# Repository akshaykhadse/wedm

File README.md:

# Power Supply Design for Wire EDM Cutting of Silicon

Part of project titled *Modelling and Control of Wire Electro Discharge Machining Processes for Cutting of Silicon Wafers*.

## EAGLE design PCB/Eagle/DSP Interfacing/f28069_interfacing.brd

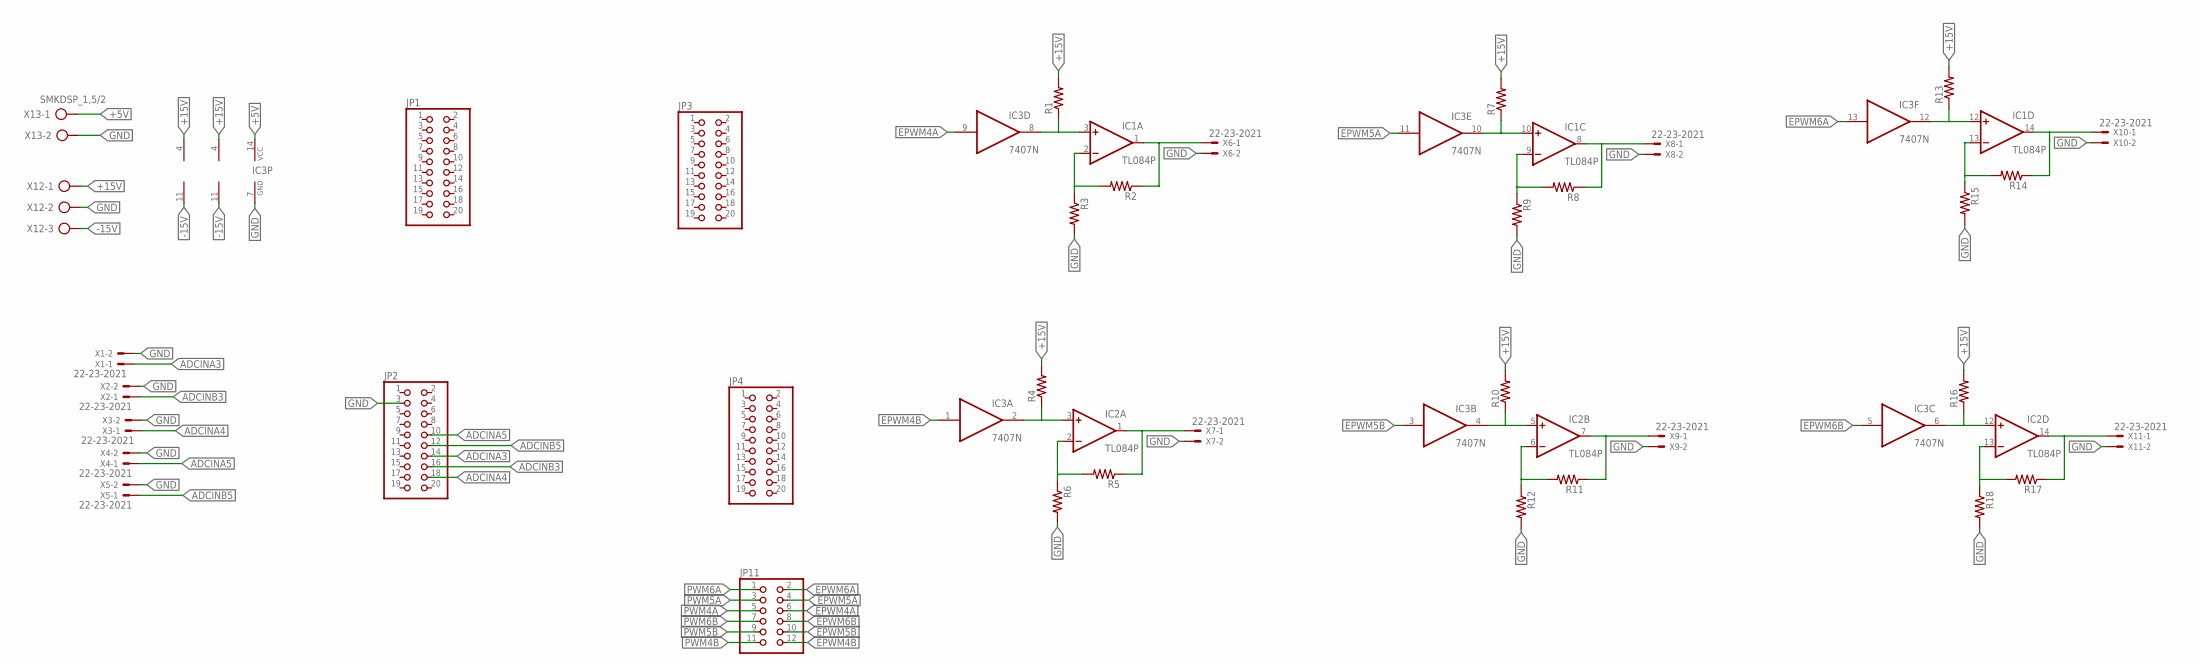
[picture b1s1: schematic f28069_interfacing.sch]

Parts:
IC1, IC2: TL084P; DIL14
IC3: 7407N; DIL14
JP1, JP2, JP3, JP4: PINHD-2X10; 2X10
JP11: PINHD-2X6; 2X06
R1, R2, R3, R4, R5, R6, R7, R8, R9, R10, R11, R12, R13, R14, R15, R16, R17, R18: R-US_0207/10; 0207/10
X1, X2, X3, X4, X5, X6, X7, X8, X9, X10, X11: 22-23-2021
X12: AK300/3
X13: SMKDSP_1,5/2

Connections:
+5V: IC3.14 (VCC), X13.1
+15V: IC1.4 (V+), IC2.4 (V+), R1.2, R4.2, R7.2, R10.2, R13.2, R16.2, X12.1
-15V: IC1.11 (V-), IC2.11 (V-), X12.3
ADCINA3: JP2.14, X1.1
ADCINA4: JP2.18, X3.1
ADCINA5: JP2.10, X4.1
ADCINB3: JP2.16, X2.1
ADCINB5: JP2.12, X5.1
EPWM4A: IC3.9 (I), JP11.6
EPWM4B: IC3.1 (I), JP11.12
EPWM5A: IC3.11 (I), JP11.4
EPWM5B: IC3.3 (I), JP11.10
EPWM6A: IC3.13 (I), JP11.2
EPWM6B: IC3.5 (I), JP11.8
GND: IC3.7 (GND), JP2.3, R3.2, R6.2, R9.2, R12.2, R15.2, R18.2, X1.2, X2.2, X3.2, X4.2, X5.2, X6.2, X7.2, X8.2, X9.2, X10.2, X11.2, X12.2, X13.2
unnamed: IC1.2 (-IN), R2.2, R3.1
unnamed: IC1.1 (OUT), R2.1, X6.1
unnamed: IC1.3 (+IN), IC3.8 (O), R1.1
unnamed: IC2.1 (OUT), R5.1, X7.1
unnamed: IC2.3 (+IN), IC3.2 (O), R4.1
unnamed: IC2.2 (-IN), R5.2, R6.1
unnamed: IC1.8 (OUT), R8.1, X8.1
unnamed: IC1.10 (+IN), IC3.10 (O), R7.1
unnamed: IC1.9 (-IN), R8.2, R9.1
unnamed: IC2.7 (OUT), R11.1, X9.1
unnamed: IC2.5 (+IN), IC3.4 (O), R10.1
unnamed: IC2.6 (-IN), R11.2, R12.1
unnamed: IC1.14 (OUT), R14.1, X10.1
unnamed: IC1.12 (+IN), IC3.12 (O), R13.1
unnamed: IC1.13 (-IN), R14.2, R15.1
unnamed: IC2.14 (OUT), R17.1, X11.1
unnamed: IC2.12 (+IN), IC3.6 (O), R16.1
unnamed: IC2.13 (-IN), R17.2, R18.1
PWM4A: JP11.5
PWM4B: JP11.11
PWM5A: JP11.3
PWM5B: JP11.9
PWM6A: JP11.1
PWM6B: JP11.7

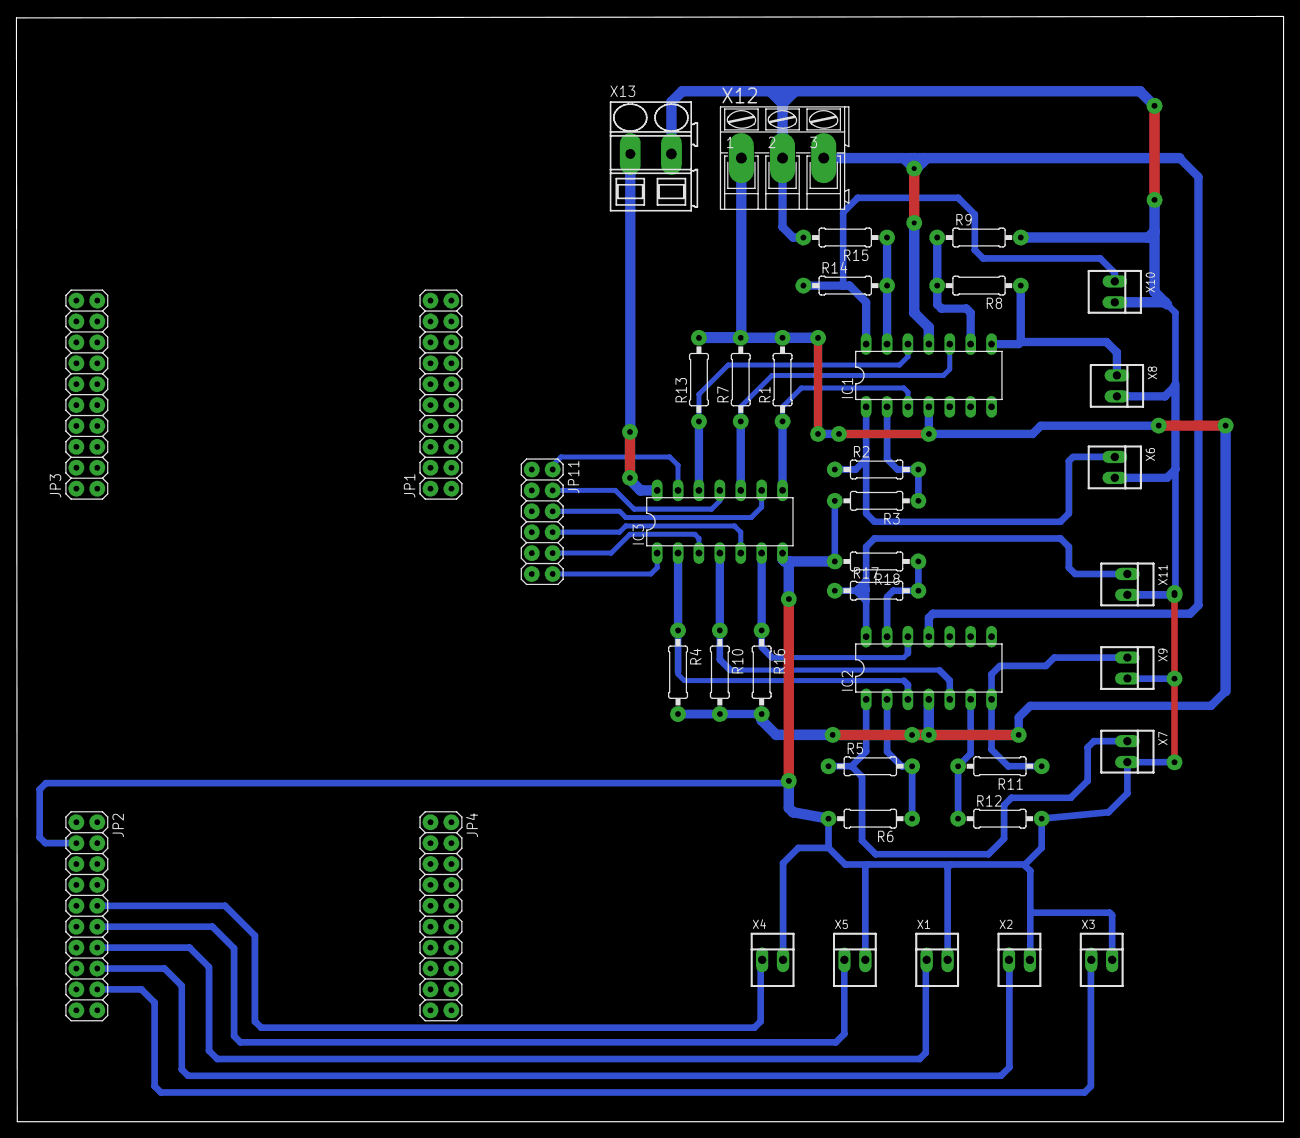
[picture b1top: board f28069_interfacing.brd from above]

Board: 2 copper layers, 154.0 x 134.3 mm, 39 parts (0 on the bottom side), 33 nets.

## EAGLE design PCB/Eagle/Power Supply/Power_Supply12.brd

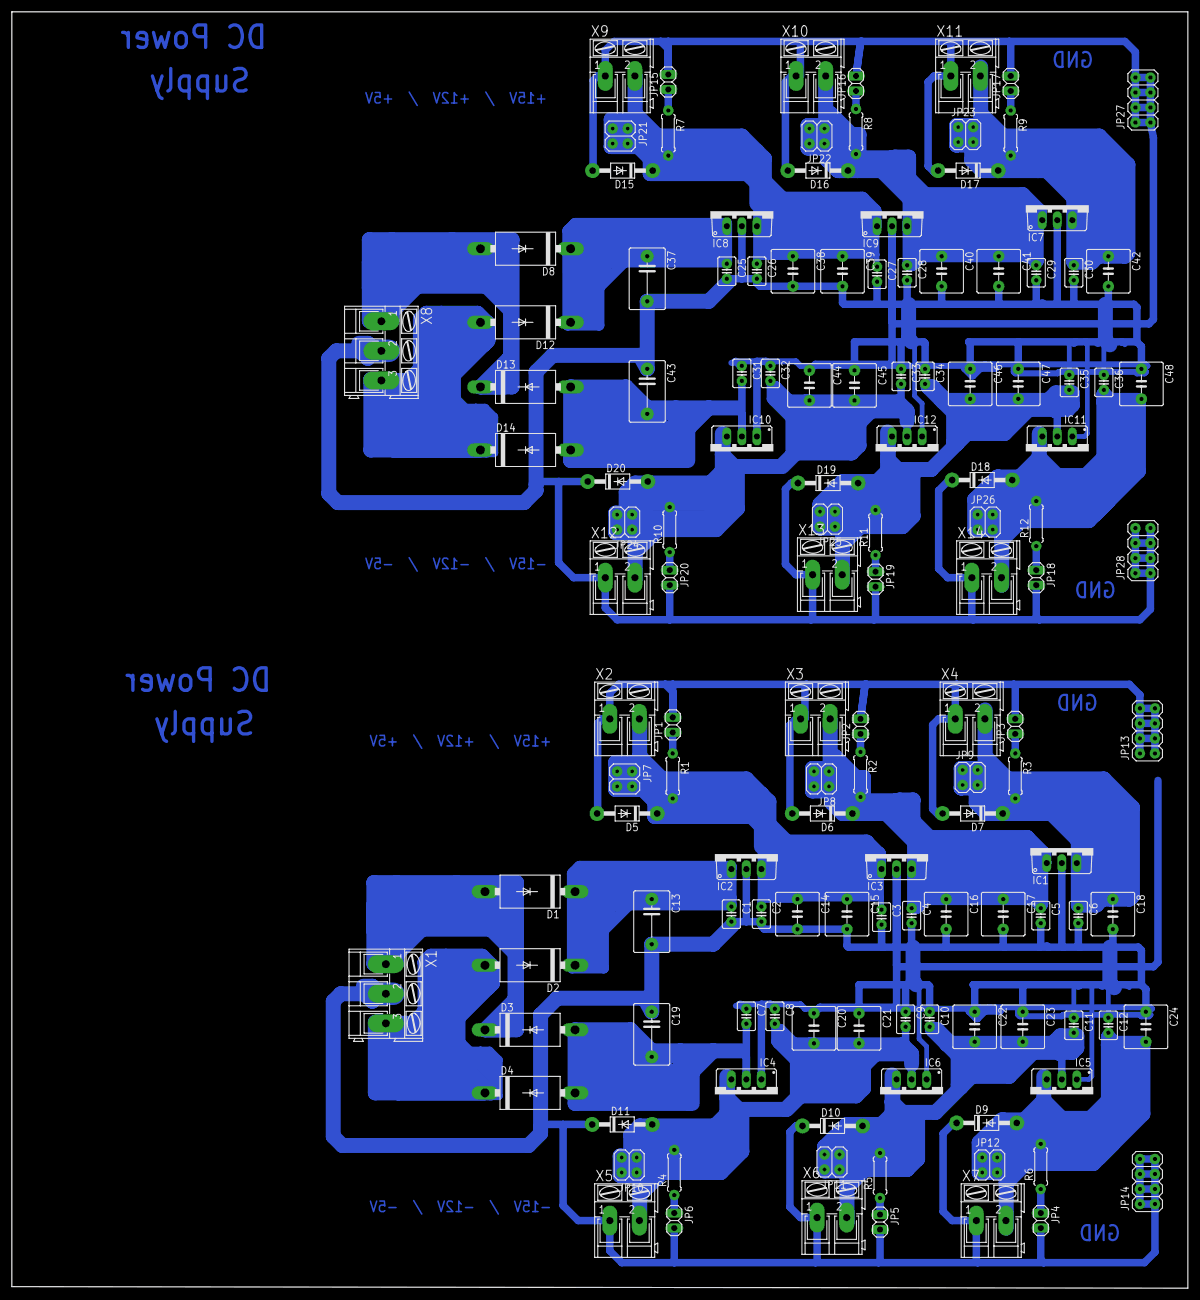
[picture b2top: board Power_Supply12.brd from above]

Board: 2 copper layers, 198.9 x 215.8 mm, 134 parts (0 on the bottom side), 34 nets.

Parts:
C1, C2, C3, C4, C5, C6, C7, C8, C9, C10, C11, C12, C25, C26, C27, C28, C29, C30, C31, C32, C33, C34, C35, C36: C025-030X050
C13, C19, C37, C43: C075-063X106
C14, C15, C16, C17, C18, C20, C21, C22, C23, C24, C38, C39, C40, C41, C42, C44, C45, C46, C47, C48: C050-075X075
D1, D2, D3, D4, D8, D12, D13, D14: 1N5400; DO201-15
D5, D6, D7, D9, D10, D11, D15, D16, D17, D18, D19, D20: 1N4004; DO41-10
IC1, IC7: 7805TV; TO220V
IC2, IC8: 7815TV; TO220V
IC3, IC9: 7812TV; TO220V
IC4, IC5, IC6, IC10, IC11, IC12: 79XXS
JP1, JP2, JP3, JP4, JP5, JP6, JP15, JP16, JP17, JP18, JP19, JP20: 1X02
JP7, JP8, JP9, JP10, JP11, JP12, JP21, JP22, JP23, JP24, JP25, JP26: 2X02
JP13, JP14, JP27, JP28: 2X04
R1, R2, R3, R4, R5, R6, R7, R8, R9, R10, R11, R12: 0207/7
X1, X8: AK300/3
X2, X3, X4, X5, X6, X7, X9, X10, X11, X12, X13, X14: AK300/2

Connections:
unnamed: C1.1, C13.1, D1.C, D2.C, IC2.1
unnamed: JP20.1, R10.1
unnamed: C2.1, C3.1, C14.1, C15.1, D5.C, IC2.3, IC3.1, JP7.1, JP7.2, JP7.3, JP7.4, R1.2, X2.2
unnamed: JP19.1, R11.1
unnamed: JP18.1, R12.1
unnamed: D2.A, D4.C, X1.3
unnamed: C1.2, C2.2, C3.2, C4.2, C5.2, C6.2, C7.1, C8.1, C9.1, C10.1, C11.1, C12.1, C13.2, C14.2, C15.2, C16.2, C17.2, C18.2, C19.1, C20.1, C21.1, C22.1, C23.1, C24.1, D5.A, D6.A, D7.A, D9.C, D10.C, D11.C, IC1.2, IC2.2, IC3.2, IC4.GND, IC5.GND, IC6.GND, JP1.2, JP2.2, JP3.2, JP4.2, JP5.2, JP6.2, JP13.1, JP13.2, JP13.3, JP13.4, JP13.5, JP13.6, JP13.7, JP13.8, JP14.1, JP14.2, JP14.3, JP14.4, JP14.5, JP14.6, JP14.7, JP14.8, X1.2, X2.1, X3.1, X4.1, X5.1, X6.1, X7.1
unnamed: C4.1, C5.1, C16.1, C17.1, D6.C, IC1.1, IC3.3, JP8.1, JP8.2, JP8.3, JP8.4, R2.2, X3.2
unnamed: JP17.1, R9.1
unnamed: C6.1, C18.1, D7.C, IC1.3, JP9.1, JP9.2, JP9.3, JP9.4, R3.2, X4.2
unnamed: JP6.1, R4.1
unnamed: JP16.1, R8.1
unnamed: JP5.1, R5.1
unnamed: JP4.1, R6.1
unnamed: JP15.1, R7.1
unnamed: JP3.1, R3.1
unnamed: D8.A, D13.C, X8.1
unnamed: JP2.1, R2.1
unnamed: JP1.1, R1.1
unnamed: D1.A, D3.C, X1.1
unnamed: C8.2, C9.2, C20.2, C21.2, D11.A, IC4.OUT, IC6.IN, JP10.1, JP10.2, JP10.3, JP10.4, R4.2, X5.2
unnamed: C10.2, C11.2, C22.2, C23.2, D10.A, IC5.IN, IC6.OUT, JP11.1, JP11.2, JP11.3, JP11.4, R5.2, X6.2
unnamed: C7.2, C19.2, D3.A, D4.A, IC4.IN
unnamed: C31.2, C43.2, D13.A, D14.A, IC10.IN
unnamed: C12.2, C24.2, D9.A, IC5.OUT, JP12.1, JP12.2, JP12.3, JP12.4, R6.2, X7.2
unnamed: C25.1, C37.1, D8.C, D12.C, IC8.1
unnamed: C26.1, C27.1, C38.1, C39.1, D15.C, IC8.3, IC9.1, JP21.1, JP21.2, JP21.3, JP21.4, R7.2, X9.2
unnamed: C28.1, C29.1, C40.1, C41.1, D16.C, IC7.1, IC9.3, JP22.1, JP22.2, JP22.3, JP22.4, R8.2, X10.2
unnamed: C30.1, C42.1, D17.C, IC7.3, JP23.1, JP23.2, JP23.3, JP23.4, R9.2, X11.2
unnamed: C32.2, C33.2, C44.2, C45.2, D20.A, IC10.OUT, IC12.IN, JP24.1, JP24.2, JP24.3, JP24.4, R10.2, X12.2
unnamed: C34.2, C35.2, C46.2, C47.2, D19.A, IC11.IN, IC12.OUT, JP25.1, JP25.2, JP25.3, JP25.4, R11.2, X13.2
unnamed: C36.2, C48.2, D18.A, IC11.OUT, JP26.1, JP26.2, JP26.3, JP26.4, R12.2, X14.2
unnamed: D12.A, D14.C, X8.3
unnamed: C25.2, C26.2, C27.2, C28.2, C29.2, C30.2, C31.1, C32.1, C33.1, C34.1, C35.1, C36.1, C37.2, C38.2, C39.2, C40.2, C41.2, C42.2, C43.1, C44.1, C45.1, C46.1, C47.1, C48.1, D15.A, D16.A, D17.A, D18.C, D19.C, D20.C, IC7.2, IC8.2, IC9.2, IC10.GND, IC11.GND, IC12.GND, JP15.2, JP16.2, JP17.2, JP18.2, JP19.2, JP20.2, JP27.1, JP27.2, JP27.3, JP27.4, JP27.5, JP27.6, JP27.7, JP27.8, JP28.1, JP28.2, JP28.3, JP28.4, JP28.5, JP28.6, JP28.7, JP28.8, X8.2, X9.1, X10.1, X11.1, X12.1, X13.1, X14.1

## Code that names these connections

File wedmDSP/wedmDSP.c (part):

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//! - log      => Logged Values
//
//! Pin Connections:
//! - ADCINA4 => Pin69
//! - ADCINB3 => Pin68
//! - ADCINA3 => Pin67
//! - ADCINB5 => Pin66
//! - ADCINA5 => Pin65
//!
//! - EPWM4A  => Pin80
//! - EPWM4B  => Pin79
//! - EPWM5A  => Pin78
//! - EPWM5B  => Pin77
//! - EPWM6A  => Pin76
//! - EPWM6B  => Pin75
//!
//! - GPIO22 => Pin8
//!
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#define EPWM4_CLKDIV 0 //EPWM4 CLKDIV

#define EPWM5_PER 4560     // EPWM5 Period
#define EPWM5A_DUTY 0.2    // EPWM5A Duty
#define EPWM5B_DUTY 0   // EPWM5B Duty
#define EPWM5_HSPCLKDIV 0 //EPWM5 HSPCLKDIV
#define EPWM5_CLKDIV 0 //EPWM5 CLKDIV

#define EPWM6_PER 9500     // EPWM6 Period
#define EPWM6A_DUTY 0.5    // EPWM6A Duty
#define EPWM6B_DUTY 0   // EPWM6B Duty
#define EPWM6_HSPCLKDIV 3 //EPWM6 HSPCLKDIV
#define EPWM6_CLKDIV 4 //EPWM6 CLKDIV

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    AdcRegs.ADCCTL2.bit.CLKDIV4EN   = 0;

    // Channel select for SOCs
    AdcRegs.ADCSOC0CTL.bit.CHSEL    = 5;    // set SOC0 channel select to ADCINA5
    AdcRegs.ADCSOC1CTL.bit.CHSEL    = 13;   // set SOC1 channel select to ADCINB5
    AdcRegs.ADCSOC2CTL.bit.CHSEL    = 3;    // set SOC2 channel select to ADCINA3
    AdcRegs.ADCSOC3CTL.bit.CHSEL    = 11;   // set SOC3 channel select to ADCINB3
    AdcRegs.ADCSOC4CTL.bit.CHSEL    = 4;    // set SOC4 channel select to ADCINA4

    // Set SOC0 start trigger on CPU TIMER 0 Interrupt
    // due to round-robin SOC0 converts in order SOC0, SOC1, ..., SOC4
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
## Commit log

2017-09-13 Stylised PID Model
2017-09-13 Added Snubber Calculations
    - Added Snubber Calculations for Qd in mast_conv.m in PID
    - Updated Model accordingly
    `
2017-09-13 Created Folder for Dependencies
    - Created seperate folder for dependencies like syms2tf
    - Updated 04 PID/mast_conv.m accordingly
    ** Common files would reside in this directory from now on
2017-09-14 Updated for 50 KHz
    - Updated PID model for 50 KHz
    - Added README.md
2017-09-14 Changed Machining Time to 200us
    - Changed Machining time to 200us
    - Added conversion to discrete time TF
2017-09-14 Tuned PID Controllers
    - Tuned PID Controllers
    - Added delay between Current and Voltage source operation
    - Modified README.md
2017-09-14 Added documentation
2017-09-14 Set theme jekyll-theme-cayman
2017-09-14 Added Download Links
2017-09-14 Moving docs to gh-pages branch
2017-09-16 Simulated Tastekin Paper
    - Simulated Tastekin paper in `05 Tastekin` folder
    - Updated component list
2017-09-18 RC Snubber
    - Renamed PID simulation file
    - Reset Qd Simulink Block parameters to all default values
    - Implemented RC Snubber (Diode is commented)
    - Recorded waveforms and circuit
    - Corrected the names of switches in load
2017-09-18 Implemented RCD Snubber
    - Uncommented diode
    - Recorded waveforms
2017-09-18 Finalised RC Snubber
2017-09-18 Changed Measurement Blocks' Names
2017-09-18 Fixed D1 Scope
2017-09-18 Updated PID
    - Split master_cov.m
    - Added Compensator blocks
    - Compensator blocks ane not yet tuned
2017-09-21 Updated Component Sheet
    - Changed BOM1.xlsx
    - Added Datat generation code
2017-09-26 Working 2
    - Deduced logic for l and c values
2017-09-27 Current Mode Control
    - Using PID
    - 100 time original L1 value
2017-09-29 Working 2
    - Fixed logic for device selection
    - Tuned Controllers
    - Fixed PWM Issue
2017-10-05 Corrected Comments
2017-10-12 Changed folder structure and cleanup
    - Removed incorrect files
    - Moved everythinh to root
    - Spreadsheet for component values now moved to google drive
2017-10-12 Renamed Files
2017-10-12 Consolidated everything
2017-12-11 Before Stage 2
2018-01-04 Updated Structure
2018-02-11 Add PCB design files and slide programs
    - PCB design files in root/PCB
    - Slide programs in root/Slide Programs
2018-02-11 Changes as of 25th Jan, 2018
    - Add floating scopes and scope viewers
    - Split master_conv2 script
    - Add power calculations
2018-02-12 Add comparison of current source with normal buck converter
2018-02-14 Fixed SVG files not showing
    - Removed *.svg from .gitignore
2018-02-15 Add comparison with normal files and CAD model
    - Add files for comparison of voltage and current source with normal
    buck converter. Run 'master1.m' to use
    - Add SolidWorks model
2018-02-15 Fix voltage source bug
    - Fixed the issue of compensator on modified voltage source causing
    instability
2018-02-15 Add plots for SRG Talk
    - Add bode and pz plots for SRG talk to 'Documentation/srg_plots'
2018-02-26 Prepare for SRG talk
    - Imporve graphs
    - Display poles
    - Improve comparison between normal and modified buck converter topologies
2018-03-01 Add Discrete Controller
    - Add discre current and voltage source controller using discrete tf
    block
2018-03-03 Fix Discrete Controllers
    - Make VS controller usinf z^-1 blocks
    - Add ZOH Block
    - Change Simulation type to continous from powergui
    - Previous error was due to sampling period of 0.01*1/f_sw in powergui block
2018-03-27 Add PCB files from Proteus
    - Cleaned up DipTrace PCB files
    - Added Proteus PCB files
2018-04-06 Change figures for PDES paper
    - Reduce size of buck converter comparison figures
    - Corrected Qd in conv-top-master
2018-04-06 Add pole locus plot script and debug end to end run
    - Add script 'pole_locus.m' to plot variation of poles of both the sources with change in values of L and C
    - Naming conventions improved in 'compensator_design.m' and 'modelling.m' to avoid replacing transfer fuctions.
    - Naming conventions improved in 'normal_buck_comparison_cs.m' and 'normal_buck_comparison_cs.m' to avoid replacing of compensator numerators and denominators, and original transfer functions
    - Hard coded 'c2_val' from 'master_conv2.m' at the end of 'normal_buck_comparison_cs.m'
2018-04-07 Match upto Makarand's paper changes - 1
    - Add dicscrete compenstor for current source using basic blocks
    - Add pulsed reference in PID for current source and corresponding vlaue
    changes
    - Sanitize 'mast_conv2.m'. Move clearing part to 'master1.m'
    - Stylize all the scopes and zooms (not completed)
2018-04-07 Match upto Makarand's paper changes - 1
    - Fixed controller scopes issue
2018-04-07 Add code to generate figures
    - Add code to generate required figures for PDES Paper in 'master1.m'
2018-04-07 Add more PDES paper figures script
    - Backup and restore logic for temperorily changed variables refined
    - Seperate script for PDES figures generation.
    - Added variation of poles with passive component values
2018-04-07 Removed obsolete files
2018-04-10 Improvements to paper figures
    - rl1 and rl2 increased
    - Optimised 'ploes_locus.m' and 'pdes_figures.m'
    - PDES figures exported to PDF
    - Naming improved in 'normal_buck_comparison_*s.m' files
2018-04-11 Add equations to PDES figures
    - Add equations ot comparison figures
    - Add 'convert_pdf.bat' to convert svg to pdfs
2018-04-12 Add compenstor bode plots in pdes formatting
    - Added code in 'pdes_figures.m' to format compensator performance bode
    plots
    - Fixed pdf cropping in matlab generated figures
2018-04-12 Minor naming improvements
2018-04-14 Update diagrams, Change rl1 value
    - Updated 2quad and buck svg files with i0hat or v0hat/dhat
    - rl1 value changed to 100uH (Courtesy Mak) and updated all pdes
    diagrams
    - Added plot for current source inductor power
    - Changed reference selection in 'powersupply.slx' to variable based
    switch
2018-04-30 Add DSP code
    - Add DSP CCS project in 'wedmDSP' directory
    - Paste 'wedmDSP' directory in 'C:\ti\c2000\C2000Ware_1_00_04_00\device_support\f2806x\examples\c28'
2018-05-02 Add ADC code to wedmDSP
2018-05-02 Add ePWM code to wedmDSP
2018-05-11 Working DSP code for measurement and PWM
2018-05-29 Fixed Frequency Issues
2018-05-30 Updated Duty Cycles in DSP
2018-06-17 Updated DSP Code, PCB Files
2018-06-30 Clean after Stage2
2018-06-30 Added calibration
2018-07-10 Added approval sheet
